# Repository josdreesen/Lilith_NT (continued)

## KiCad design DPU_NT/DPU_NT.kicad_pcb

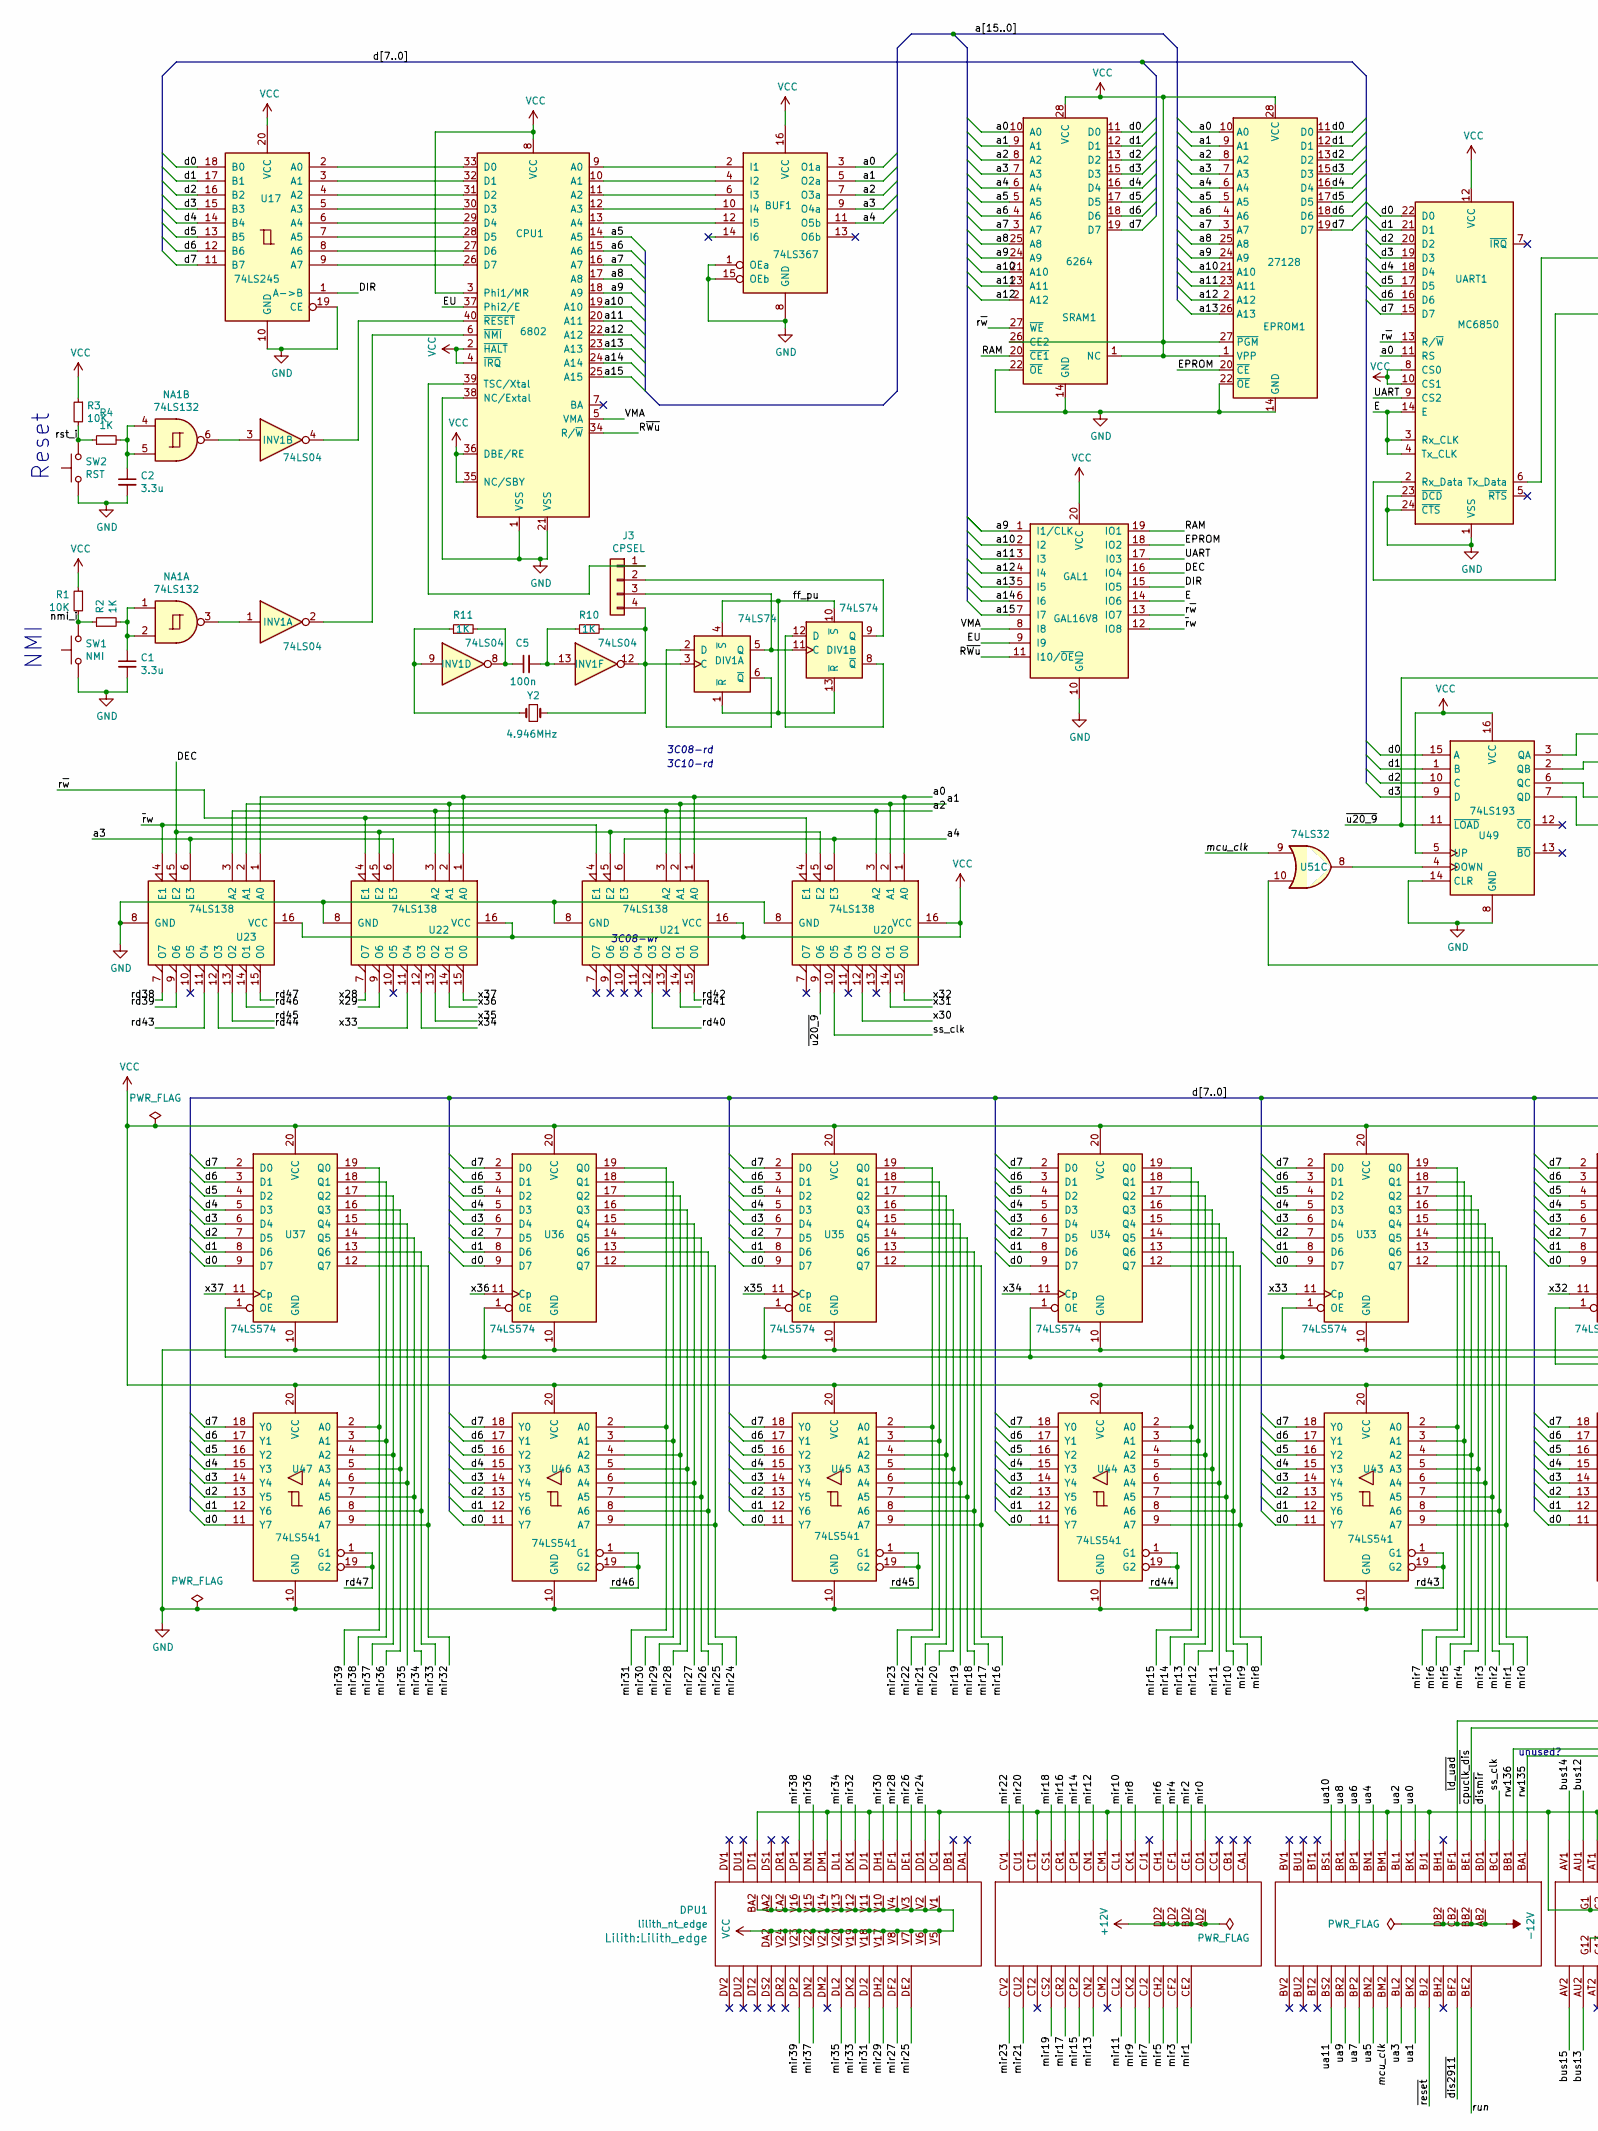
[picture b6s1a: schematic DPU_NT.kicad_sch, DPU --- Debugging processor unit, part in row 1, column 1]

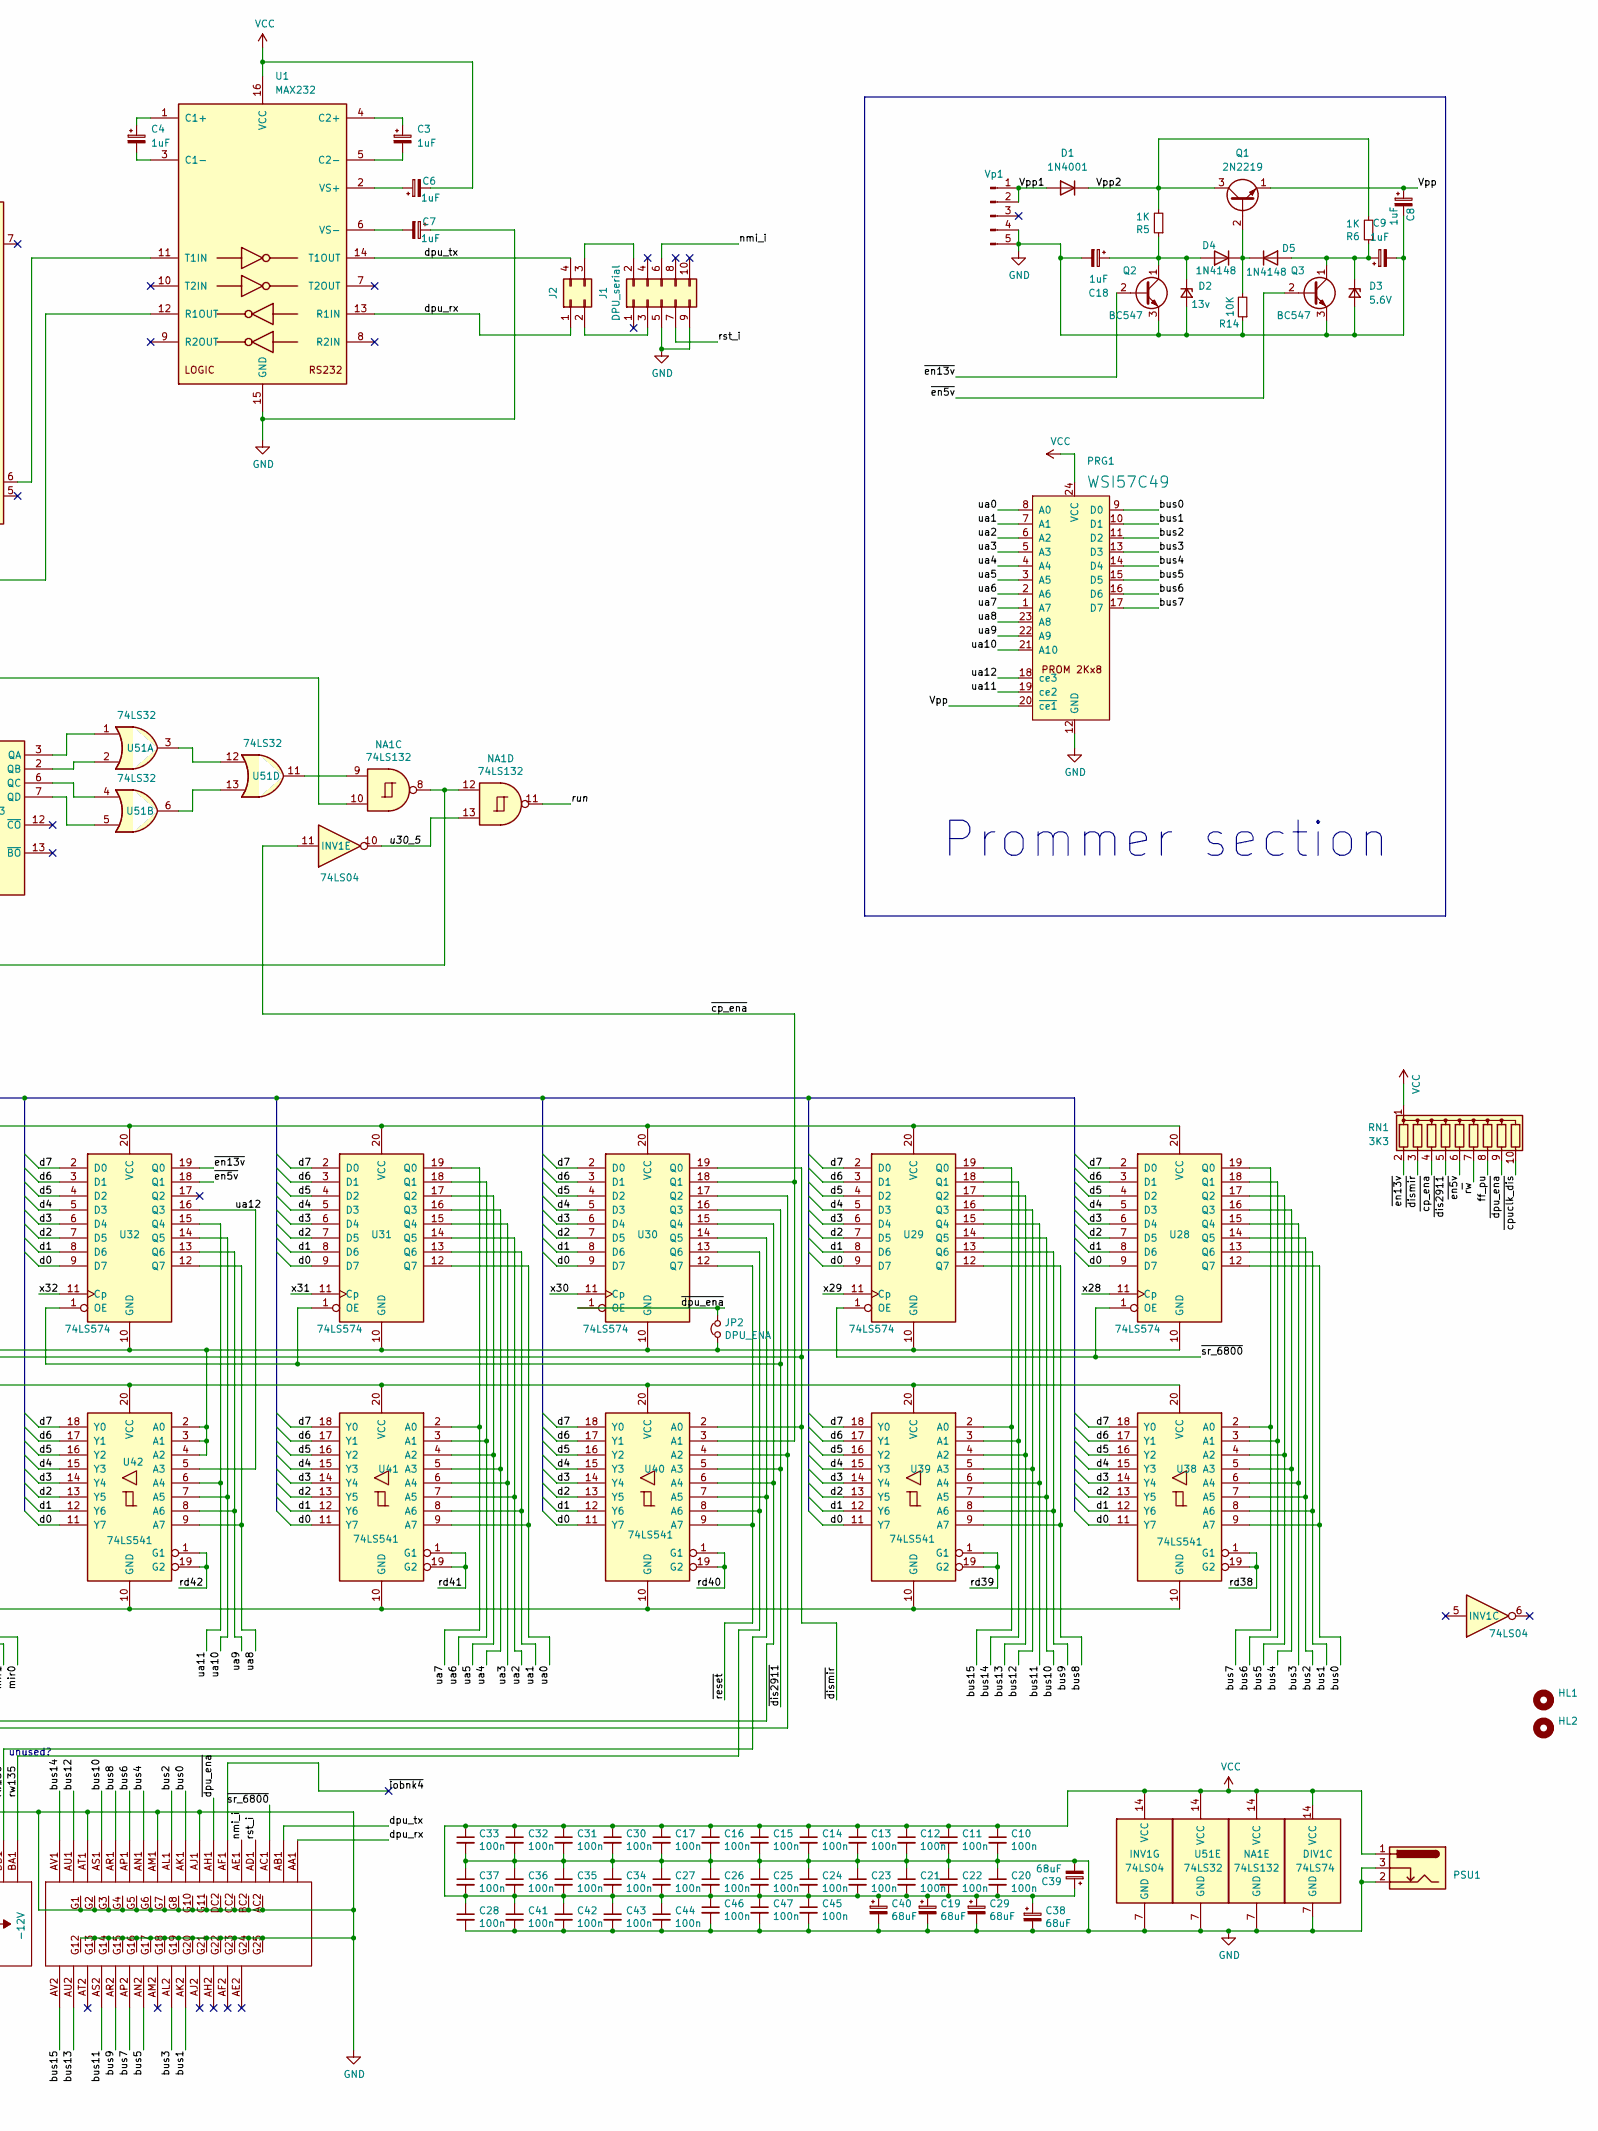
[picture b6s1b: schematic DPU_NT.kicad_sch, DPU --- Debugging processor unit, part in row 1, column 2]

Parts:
BUF1: 74LS367; DIP-16_W7.62mm
C1, C2: 3.3u; CP_Radial_D5.0mm_P2.50mm
C3, C4, C6, C7, C8, C9, C18: 1uF; CP_Radial_Tantal_D5.0mm_P2.50mm
C5: 100n; C_Rect_L7.0mm_W3.5mm_P5.00mm
C10, C11, C12, C13, C14, C15, C16, C17, C20, C21, C22, C23, C24, C25, C26, C27, C30, C31, C32, C33, C34, C35, C36, C37, C42, C45, C46, C47: 100n; C_1206_3216Metric_Pad1.33x1.80mm_HandSolder
C19, C29, C38, C39, C40: 68uF; CP_PHP
C28, C41, C43, C44: 100n; C_0805_2012Metric
CPU1: 6802; DIP-40_W15.24mm
D1: 1N4001; D_DO-35_SOD27_P7.62mm_Horizontal
D2: 13v; D_DO-35_SOD27_P7.62mm_Horizontal
D3: 5.6V; D_DO-35_SOD27_P7.62mm_Horizontal
D4, D5: 1N4148; D_DO-35_SOD27_P7.62mm_Horizontal
DIV1: 74LS74; DIP-14_W7.62mm
DPU1: lilith_nt_edge; Lilith_edge
EPROM1: 27128; DIP-28_W15.24mm
GAL1: GAL16V8; DIP-20_W7.62mm_Socket
HL1, HL2: MountingHole; Handle
INV1: 74LS04; DIP-14_W7.62mm_LongPads
J1: DPU_serial; PinHeader_2x05_P2.54mm_Vertical
J2: Conn_02x02_Counter_Clockwise; PinHeader_2x02_P2.54mm_Vertical
J3: CPSEL; PinHeader_1x04_P2.54mm_Vertical
JP2: DPU_ENA; PinHeader_1x02_P2.54mm_Vertical
NA1: 74LS132; DIP-14_W7.62mm
PRG1: WSI57C49; DuoDil24
PSU1: Barrel_Jack_Switch; BarrelJack_GCT_DCJ200-10-A_Horizontal
Q1: 2N2219; TO-39-3
Q2, Q3: BC547; TO-92_Inline
R1, R3, R14: 10K; R_Axial_DIN0207_L6.3mm_D2.5mm_P7.62mm_Horizontal
R2, R4, R5, R6, R10, R11: 1K; R_Axial_DIN0207_L6.3mm_D2.5mm_P7.62mm_Horizontal
RN1: 3K3; R_Array_SIP10
SRAM1: 6264; DIP-28_W15.24mm
SW1: NMI; SW_PUSH_6mm
SW2: RST; SW_PUSH_6mm
U1: MAX232; DIP-16_W7.62mm
U17: 74LS245; DIP-20_W7.62mm
U20, U21, U22, U23: 74LS138; DIP-16_W7.62mm
U28, U29, U30, U31, U32, U33, U34, U35, U36, U37: 74LS574; DIP-20_W7.62mm
U38, U39, U40, U41, U42, U43, U44, U45, U46, U47: 74LS541; DIP-20_W7.62mm
U49: 74LS193; DIP-16_W7.62mm
U51: 74LS32; DIP-14_W7.62mm
UART1: MC6850; DIP-24_W15.24mm
Vp1: Conn_01x05_Pin; PinHeader_1x05_P2.54mm_Horizontal
Y2: 4.946MHz; Crystal_HC52-8mm_Horizontal

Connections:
+12V: DPU1.AD2, DPU1.BD2, DPU1.CD2, DPU1.DD2
-12V: DPU1.AB2, DPU1.BB2, DPU1.CB2, DPU1.DB2
/DEC: GAL1.16 (IO4), U20.5 (E2), U21.5 (E2), U22.5 (E2), U23.5 (E2)
/DIR: GAL1.15 (IO5), U17.1 (A->B)
/E: GAL1.14 (IO6), UART1.3 (Rx_CLK), UART1.4 (Tx_CLK), UART1.14 (E)
/EPROM: EPROM1.20 (~CE), GAL1.18 (IO2)
/EU: CPU1.37 (Phi2/E), GAL1.9 (I9)
/RAM: GAL1.19 (IO1), SRAM1.20 (~CE1)
/R~Wu: CPU1.34 (R/~W), GAL1.11 (I10/~OE)
/UART: GAL1.17 (I03), UART1.9 (CS2)
/VMA: CPU1.5 (VMA), GAL1.8 (I8)
/Vpp: C8.1, PRG1.20 (~ce1), Q1.1 (E)
/Vpp1: D1.2 (A), Vp1.1, Vp1.2
/Vpp2: D1.1 (K), Q1.3 (C), R5.2, R6.2
/a0: BUF1.3 (O1a), EPROM1.10 (A0), SRAM1.10 (A0), U20.1 (A0), U21.1 (A0), U22.1 (A0), U23.1 (A0), UART1.11 (RS)
/a1: BUF1.5 (O2a), EPROM1.9 (A1), SRAM1.9 (A1), U20.2 (A1), U21.2 (A1), U22.2 (A1), U23.2 (A1)
/a2: BUF1.7 (O3a), EPROM1.8 (A2), SRAM1.8 (A2), U20.3 (A2), U21.3 (A2), U22.3 (A2), U23.3 (A2)
/a3: BUF1.9 (O4a), EPROM1.7 (A3), SRAM1.7 (A3), U22.6 (E3), U23.6 (E3)
/a4: BUF1.11 (O5b), EPROM1.6 (A4), SRAM1.6 (A4), U20.6 (E3), U21.6 (E3)
/a5: CPU1.14 (A5), EPROM1.5 (A5), SRAM1.5 (A5)
/a6: CPU1.15 (A6), EPROM1.4 (A6), SRAM1.4 (A6)
/a7: CPU1.16 (A7), EPROM1.3 (A7), SRAM1.3 (A7)
/a8: CPU1.17 (A8), EPROM1.25 (A8), SRAM1.25 (A8)
/a9: CPU1.18 (A9), EPROM1.24 (A9), GAL1.1 (I1/CLK), SRAM1.24 (A9)
/a10: CPU1.19 (A10), EPROM1.21 (A10), GAL1.2 (I2), SRAM1.21 (A10)
/a11: CPU1.20 (A11), EPROM1.23 (A11), GAL1.3 (I3), SRAM1.23 (A11)
/a12: CPU1.22 (A12), EPROM1.2 (A12), GAL1.4 (I4), SRAM1.2 (A12)
/a13: CPU1.23 (A13), EPROM1.26 (A13), GAL1.5 (I5)
/a14: CPU1.24 (A14), GAL1.6 (I6)
/a15: CPU1.25 (A15), GAL1.7 (I7)
/bus0: DPU1.AK1, PRG1.9 (D0), U28.12 (Q7), U38.9 (A7)
/bus1: DPU1.AK2, PRG1.10 (D1), U28.13 (Q6), U38.8 (A6)
/bus2: DPU1.AL1, PRG1.11 (D2), U28.14 (Q5), U38.7 (A5)
/bus3: DPU1.AL2, PRG1.13 (D3), U28.15 (Q4), U38.6 (A4)
/bus4: DPU1.AN1, PRG1.14 (D4), U28.16 (Q3), U38.5 (A3)
/bus5: DPU1.AN2, PRG1.15 (D5), U28.17 (Q2), U38.4 (A2)
/bus6: DPU1.AP1, PRG1.16 (D6), U28.18 (Q1), U38.3 (A1)
/bus7: DPU1.AP2, PRG1.17 (D7), U28.19 (Q0), U38.2 (A0)
/bus8: DPU1.AR1, U29.12 (Q7), U39.9 (A7)
/bus9: DPU1.AR2, U29.13 (Q6), U39.8 (A6)
/bus10: DPU1.AS1, U29.14 (Q5), U39.7 (A5)
/bus11: DPU1.AS2, U29.15 (Q4), U39.6 (A4)
/bus12: DPU1.AU1, U29.16 (Q3), U39.5 (A3)
/bus13: DPU1.AU2, U29.17 (Q2), U39.4 (A2)
/bus14: DPU1.AV1, U29.18 (Q1), U39.3 (A1)
/bus15: DPU1.AV2, U29.19 (Q0), U39.2 (A0)
/d0: EPROM1.11 (D0), SRAM1.11 (D0), U17.18 (B0), U28.9 (D7), U29.9 (D7), U30.9 (D7), U31.9 (D7), U32.9 (D7), U33.9 (D7), U34.9 (D7), U35.9 (D7), U36.9 (D7), U37.9 (D7), U38.11 (Y7), U39.11 (Y7), U40.11 (Y7), U41.11 (Y7), U42.11 (Y7), U43.11 (Y7), U44.11 (Y7), U45.11 (Y7), U46.11 (Y7), U47.11 (Y7), U49.15 (A), UART1.22 (D0)
/d1: EPROM1.12 (D1), SRAM1.12 (D1), U17.17 (B1), U28.8 (D6), U29.8 (D6), U30.8 (D6), U31.8 (D6), U32.8 (D6), U33.8 (D6), U34.8 (D6), U35.8 (D6), U36.8 (D6), U37.8 (D6), U38.12 (Y6), U39.12 (Y6), U40.12 (Y6), U41.12 (Y6), U42.12 (Y6), U43.12 (Y6), U44.12 (Y6), U45.12 (Y6), U46.12 (Y6), U47.12 (Y6), U49.1 (B), UART1.21 (D1)
/d2: EPROM1.13 (D2), SRAM1.13 (D2), U17.16 (B2), U28.7 (D5), U29.7 (D5), U30.7 (D5), U31.7 (D5), U32.7 (D5), U33.7 (D5), U34.7 (D5), U35.7 (D5), U36.7 (D5), U37.7 (D5), U38.13 (Y5), U39.13 (Y5), U40.13 (Y5), U41.13 (Y5), U42.13 (Y5), U43.13 (Y5), U44.13 (Y5), U45.13 (Y5), U46.13 (Y5), U47.13 (Y5), U49.10 (C), UART1.20 (D2)
/d3: EPROM1.15 (D3), SRAM1.15 (D3), U17.15 (B3), U28.6 (D4), U29.6 (D4), U30.6 (D4), U31.6 (D4), U32.6 (D4), U33.6 (D4), U34.6 (D4), U35.6 (D4), U36.6 (D4), U37.6 (D4), U38.14 (Y4), U39.14 (Y4), U40.14 (Y4), U41.14 (Y4), U42.14 (Y4), U43.14 (Y4), U44.14 (Y4), U45.14 (Y4), U46.14 (Y4), U47.14 (Y4), U49.9 (D), UART1.19 (D3)
/d4: EPROM1.16 (D4), SRAM1.16 (D4), U17.14 (B4), U28.5 (D3), U29.5 (D3), U30.5 (D3), U31.5 (D3), U32.5 (D3), U33.5 (D3), U34.5 (D3), U35.5 (D3), U36.5 (D3), U37.5 (D3), U38.15 (Y3), U39.15 (Y3), U40.15 (Y3), U41.15 (Y3), U42.15 (Y3), U43.15 (Y3), U44.15 (Y3), U45.15 (Y3), U46.15 (Y3), U47.15 (Y3), UART1.18 (D4)
/d5: EPROM1.17 (D5), SRAM1.17 (D5), U17.13 (B5), U28.4 (D2), U29.4 (D2), U30.4 (D2), U31.4 (D2), U32.4 (D2), U33.4 (D2), U34.4 (D2), U35.4 (D2), U36.4 (D2), U37.4 (D2), U38.16 (Y2), U39.16 (Y2), U40.16 (Y2), U41.16 (Y2), U42.16 (Y2), U43.16 (Y2), U44.16 (Y2), U45.16 (Y2), U46.16 (Y2), U47.16 (Y2), UART1.17 (D5)
/d6: EPROM1.18 (D6), SRAM1.18 (D6), U17.12 (B6), U28.3 (D1), U29.3 (D1), U30.3 (D1), U31.3 (D1), U32.3 (D1), U33.3 (D1), U34.3 (D1), U35.3 (D1), U36.3 (D1), U37.3 (D1), U38.17 (Y1), U39.17 (Y1), U40.17 (Y1), U41.17 (Y1), U42.17 (Y1), U43.17 (Y1), U44.17 (Y1), U45.17 (Y1), U46.17 (Y1), U47.17 (Y1), UART1.16 (D6)
/d7: EPROM1.19 (D7), SRAM1.19 (D7), U17.11 (B7), U28.2 (D0), U29.2 (D0), U30.2 (D0), U31.2 (D0), U32.2 (D0), U33.2 (D0), U34.2 (D0), U35.2 (D0), U36.2 (D0), U37.2 (D0), U38.18 (Y0), U39.18 (Y0), U40.18 (Y0), U41.18 (Y0), U42.18 (Y0), U43.18 (Y0), U44.18 (Y0), U45.18 (Y0), U46.18 (Y0), U47.18 (Y0), UART1.15 (D7)
/dpu_rx: DPU1.AA1, J2.1, U1.13 (R1IN)
/dpu_tx: DPU1.AB1, J2.4, U1.14 (T1OUT)
/ff_pu: DIV1.1 (~R), DIV1.4 (~S), DIV1.10 (~S), DIV1.13 (~R), RN1.8 (R7)
/mcu_clk: DPU1.BM2, U51.9
/mir0: DPU1.CD1, U33.12 (Q7), U43.9 (A7)
/mir1: DPU1.CE2, U33.13 (Q6), U43.8 (A6)
/mir2: DPU1.CE1, U33.14 (Q5), U43.7 (A5)
/mir3: DPU1.CF2, U33.15 (Q4), U43.6 (A4)
/mir4: DPU1.CF1, U33.16 (Q3), U43.5 (A3)
/mir5: DPU1.CH2, U33.17 (Q2), U43.4 (A2)
/mir6: DPU1.CH1, U33.18 (Q1), U43.3 (A1)
/mir7: DPU1.CJ2, U33.19 (Q0), U43.2 (A0)
/mir8: DPU1.CK1, U34.12 (Q7), U44.9 (A7)
/mir9: DPU1.CK2, U34.13 (Q6), U44.8 (A6)
/mir10: DPU1.CL1, U34.14 (Q5), U44.7 (A5)
/mir11: DPU1.CL2, U34.15 (Q4), U44.6 (A4)
/mir12: DPU1.CN1, U34.16 (Q3), U44.5 (A3)
/mir13: DPU1.CN2, U34.17 (Q2), U44.4 (A2)
/mir14: DPU1.CP1, U34.18 (Q1), U44.3 (A1)
/mir15: DPU1.CP2, U34.19 (Q0), U44.2 (A0)
/mir16: DPU1.CR1, U35.12 (Q7), U45.9 (A7)
/mir17: DPU1.CR2, U35.13 (Q6), U45.8 (A6)
/mir18: DPU1.CS1, U35.14 (Q5), U45.7 (A5)
/mir19: DPU1.CS2, U35.15 (Q4), U45.6 (A4)
/mir20: DPU1.CU1, U35.16 (Q3), U45.5 (A3)
/mir21: DPU1.CU2, U35.17 (Q2), U45.4 (A2)
/mir22: DPU1.CV1, U35.18 (Q1), U45.3 (A1)
/mir23: DPU1.CV2, U35.19 (Q0), U45.2 (A0)
/mir24: DPU1.DD1, U36.12 (Q7), U46.9 (A7)
/mir25: DPU1.DE2, U36.13 (Q6), U46.8 (A6)
/mir26: DPU1.DE1, U36.14 (Q5), U46.7 (A5)
/mir27: DPU1.DF2, U36.15 (Q4), U46.6 (A4)
/mir28: DPU1.DF1, U36.16 (Q3), U46.5 (A3)
/mir29: DPU1.DH2, U36.17 (Q2), U46.4 (A2)
/mir30: DPU1.DH1, U36.18 (Q1), U46.3 (A1)
/mir31: DPU1.DJ2, U36.19 (Q0), U46.2 (A0)
/mir32: DPU1.DK1, U37.12 (Q7), U47.9 (A7)
/mir33: DPU1.DK2, U37.13 (Q6), U47.8 (A6)
/mir34: DPU1.DL1, U37.14 (Q5), U47.7 (A5)
/mir35: DPU1.DL2, U37.15 (Q4), U47.6 (A4)
/mir36: DPU1.DN1, U37.16 (Q3), U47.5 (A3)
/mir37: DPU1.DN2, U37.17 (Q2), U47.4 (A2)
/mir38: DPU1.DP1, U37.18 (Q1), U47.3 (A1)
/mir39: DPU1.DP2, U37.19 (Q0), U47.2 (A0)
/nmi_i: DPU1.AE1, J1.6, R1.2, R2.1, SW1.2
/rd38: U23.7 (O7), U38.1 (G1), U38.19 (G2)
/rd39: U23.9 (O6), U39.1 (G1), U39.19 (G2)
/rd40: U21.12 (O3), U40.1 (G1), U40.19 (G2)
/rd41: U21.14 (O1), U41.1 (G1), U41.19 (G2)
/rd42: U21.15 (O0), U42.1 (G1), U42.19 (G2)
/rd43: U23.11 (O4), U43.1 (G1), U43.19 (G2)
/rd44: U23.12 (O3), U44.1 (G1), U44.19 (G2)
/rd45: U23.13 (O2), U45.1 (G1), U45.19 (G2)
/rd46: U23.14 (O1), U46.1 (G1), U46.19 (G2)
/rd47: U23.15 (O0), U47.1 (G1), U47.19 (G2)
/rst_i: DPU1.AD1, J1.7, R3.2, R4.1, SW2.2
/run: DPU1.BE2, NA1.11
/rw135: DPU1.BA1, U30.13 (Q6), U40.8 (A6)
/rw136: DPU1.BB1, U30.14 (Q5), U40.7 (A5)
/r~w: GAL1.13 (IO7), RN1.7 (R6), SRAM1.27 (~WE), U20.4 (E1), U22.4 (E1), UART1.13 (R/~W)
/ss_clk: DPU1.BC1, U20.10 (O5)
/u30_5: INV1.10, NA1.13
/ua0: DPU1.BK1, PRG1.8 (A0), U31.12 (Q7), U41.9 (A7)
/ua1: DPU1.BK2, PRG1.7 (A1), U31.13 (Q6), U41.8 (A6)
/ua2: DPU1.BL1, PRG1.6 (A2), U31.14 (Q5), U41.7 (A5)
/ua3: DPU1.BL2, PRG1.5 (A3), U31.15 (Q4), U41.6 (A4)
/ua4: DPU1.BN1, PRG1.4 (A4), U31.16 (Q3), U41.5 (A3)
/ua5: DPU1.BN2, PRG1.3 (A5), U31.17 (Q2), U41.4 (A2)
/ua6: DPU1.BP1, PRG1.2 (A6), U31.18 (Q1), U41.3 (A1)
/ua7: DPU1.BP2, PRG1.1 (A7), U31.19 (Q0), U41.2 (A0)
/ua8: DPU1.BR1, PRG1.23 (A8), U32.12 (Q7), U42.9 (A7)
/ua9: DPU1.BR2, PRG1.22 (A9), U32.13 (Q6), U42.8 (A6)
/ua10: DPU1.BS1, PRG1.21 (A10), U32.14 (Q5), U42.7 (A5)
/ua11: DPU1.BS2, PRG1.19 (ce2), U32.15 (Q4), U42.6 (A4)
/ua12: PRG1.18 (ce3), U32.16 (Q3), U42.5 (A3)
/x28: U22.7 (O7), U28.11 (Cp)
/x29: U22.9 (O6), U29.11 (Cp)
/x30: U20.12 (O3), U30.11 (Cp)
/x31: U20.14 (O1), U31.11 (Cp)
/x32: U20.15 (O0), U32.11 (Cp)
/x33: U22.11 (O4), U33.11 (Cp)
/x34: U22.12 (O3), U34.11 (Cp)
/x35: U22.13 (O2), U35.11 (Cp)
/x36: U22.14 (O1), U36.11 (Cp)
/x37: U22.15 (O0), U37.11 (Cp)
/~cp_ena: INV1.11, RN1.4 (R3), U30.18 (Q1), U40.3 (A1)
/~cpuclk_dis: DPU1.BE1, RN1.10 (R9), U30.17 (Q2), U40.4 (A2)
/~dis2911: DPU1.BF2, RN1.5 (R4), U30.16 (Q3), U31.1 (OE), U32.1 (OE), U40.5 (A3)
/~dismir: DPU1.BD1, RN1.3 (R2), U30.19 (Q0), U33.1 (OE), U34.1 (OE), U35.1 (OE), U36.1 (OE), U37.1 (OE), U40.2 (A0)
/~dpu_ena: DPU1.AH1, JP2.2, RN1.9 (R8), U30.1 (OE)
/~en5v: Q3.2 (B), RN1.6 (R5), U32.18 (Q1)
/~en13v: Q2.2 (B), RN1.2 (R1), U32.19 (Q0)
/~iobnk4: DPU1.AF1
/~ld_uad: DPU1.BF1, U30.15 (Q4), U40.6 (A4)
/~reset: DPU1.BJ2, U30.12 (Q7), U40.9 (A7)
/~rw: GAL1.12 (IO8), U21.4 (E1), U23.4 (E1)
/~sr_6800: DPU1.AC1, U28.1 (OE), U29.1 (OE)
/~u20_9: NA1.10, U20.9 (O6), U49.11 (~LOAD)
GND: BUF1.1 (OEa), BUF1.8 (GND), BUF1.15 (OEb), C1.2, C2.2, C7.1, C8.2, C9.2, C10.2, C11.2, C12.2, C13.2, C14.2, C15.2, C16.2, C17.2, C18.2, C19.2, C20.1, C21.1, C22.1, C23.1, C24.1, C25.1, C26.1, C27.1, C28.2, C29.2, C30.2, C31.2, C32.2, C33.2, C34.1, C35.1, C36.1, C37.1, C38.2, C39.2, C40.2, C41.2, C42.2, C43.2, C44.2, C45.2, C46.2, C47.2, CPU1.1 (VSS), CPU1.21 (VSS), CPU1.38 (NC/Extal), D2.2 (A), D3.2 (A), DIV1.7 (GND), DPU1.AC2, DPU1.AJ1, DPU1.AM1, DPU1.AT1, DPU1.BC2, DPU1.BJ1, DPU1.BM1, DPU1.CC2, DPU1.CM1, DPU1.CT1, DPU1.DC1, DPU1.DC2, DPU1.DJ1, DPU1.DM1, DPU1.DT1, DPU1.G1 (GND), DPU1.G2 (GND), DPU1.G3 (GND), DPU1.G4 (GND), DPU1.G5 (GND), DPU1.G6 (GND), DPU1.G7 (GND), DPU1.G8 (GND), DPU1.G10, DPU1.G11, DPU1.G12, DPU1.G13, DPU1.G14, DPU1.G15, DPU1.G16, DPU1.G17, DPU1.G18, DPU1.G19, DPU1.G20, DPU1.G21, DPU1.G22, DPU1.G23, DPU1.G24, DPU1.G25, EPROM1.14 (GND), EPROM1.22 (~OE), GAL1.10 (GND), INV1.7 (GND), J1.5, J1.9, JP2.1, NA1.7 (GND), PRG1.12 (GND), PSU1.2, PSU1.3, Q2.3 (E), Q3.3 (E), R14.1, SRAM1.14 (GND), SRAM1.22 (~OE), SW1.1, SW2.1, U1.15 (GND), U17.10 (GND), U17.19 (CE), U20.8 (GND), U21.8 (GND), U22.8 (GND), U23.8 (GND), U28.10 (GND), U29.10 (GND), U30.10 (GND), U31.10 (GND), U32.10 (GND), U33.10 (GND), U34.10 (GND), U35.10 (GND), U36.10 (GND), U37.10 (GND), U38.10 (GND), U39.10 (GND), U40.10 (GND), U41.10 (GND), U42.2 (A0), U42.3 (A1), U42.4 (A2), U42.10 (GND), U43.10 (GND), U44.10 (GND), U45.10 (GND), U46.10 (GND), U47.10 (GND), U49.8 (GND), U49.14 (CLR), U51.7 (GND), UART1.1 (VSS), UART1.23 (~DCD), UART1.24 (~CTS), Vp1.4, Vp1.5
unnamed: BUF1.2 (I1), CPU1.9 (A0)
unnamed: BUF1.4 (I2), CPU1.10 (A1)
unnamed: BUF1.6 (I3), CPU1.11 (A2)
unnamed: BUF1.10 (I4), CPU1.12 (A3)
unnamed: BUF1.12 (I5), CPU1.13 (A4)
unnamed: C1.1, NA1.1, NA1.2, R2.2
unnamed: C2.1, NA1.4, NA1.5, R4.2
unnamed: C5.1, INV1.8, R11.2
unnamed: C5.2, INV1.13, R10.1
unnamed: CPU1.33 (D0), U17.2 (A0)
unnamed: CPU1.32 (D1), U17.3 (A1)
unnamed: CPU1.31 (D2), U17.4 (A2)
unnamed: CPU1.30 (D3), U17.5 (A3)
unnamed: CPU1.29 (D4), U17.6 (A4)
unnamed: CPU1.28 (D5), U17.7 (A5)
unnamed: CPU1.27 (D6), U17.8 (A6)
unnamed: CPU1.26 (D7), U17.9 (A7)
unnamed: CPU1.39 (TSC/Xtal), J3.1
unnamed: CPU1.6 (~NMI), INV1.2
unnamed: CPU1.40 (~RESET), INV1.4
unnamed: C18.1, D2.1 (K), D4.2 (A), Q2.1 (C), R5.1
unnamed: C9.1, D3.1 (K), D5.2 (A), Q3.1 (C), R6.1
unnamed: D4.1 (K), D5.1 (K), Q1.2 (B), R14.2
unnamed: DIV1.3 (C), INV1.12, J3.4, R10.2, Y2.1
unnamed: DIV1.2 (D), DIV1.6 (~Q)
unnamed: DIV1.5 (Q), DIV1.11 (C), J3.3
unnamed: DIV1.8 (~Q), DIV1.12 (D)
unnamed: DIV1.9 (Q), J3.2
unnamed: INV1.1, NA1.3
unnamed: INV1.3, NA1.6
unnamed: INV1.9, R11.1, Y2.2
unnamed: J1.2, J2.3
unnamed: J1.3, J2.2
unnamed: NA1.9, U51.11
unnamed: NA1.8, NA1.12, U51.10
unnamed: C4.1, U1.1 (C1+)
unnamed: C4.2, U1.3 (C1-)
unnamed: C3.1, U1.4 (C2+)
unnamed: C3.2, U1.5 (C2-)
unnamed: U1.12 (R1OUT), UART1.2 (Rx_Data)
unnamed: U1.11 (T1IN), UART1.6 (Tx_Data)
unnamed: C6.1, U1.2 (VS+)
unnamed: C7.2, U1.6 (VS-)
unnamed: U49.4 (DOWN), U51.8
unnamed: U49.3 (QA), U51.1
unnamed: U49.2 (QB), U51.2
unnamed: U49.6 (QC), U51.4
unnamed: U49.7 (QD), U51.5
unnamed: U51.3, U51.12
unnamed: U51.6, U51.13
VCC: BUF1.16 (VCC), C6.2, C10.1, C11.1, C12.1, C13.1, C14.1, C15.1, C16.1, C17.1, C19.1, C20.2, C21.2, C22.2, C23.2, C24.2, C25.2, C26.2, C27.2, C28.1, C29.1, C30.1, C31.1, C32.1, C33.1, C34.2, C35.2, C36.2, C37.2, C38.1, C39.1, C40.1, C41.1, C42.1, C43.1, C44.1, C45.1, C46.1, C47.1, CPU1.2 (~HALT), CPU1.3 (Phi1/MR), CPU1.4 (~IRQ), CPU1.8 (VCC), CPU1.35 (NC/SBY), CPU1.36 (DBE/RE), DIV1.14 (VCC), DPU1.AA2, DPU1.BA2, DPU1.CA2, DPU1.DA2, DPU1.V1 (VCC), DPU1.V2 (VCC), DPU1.V3 (VCC), DPU1.V4 (VCC), DPU1.V5 (VCC), DPU1.V6 (VCC), DPU1.V7 (VCC), DPU1.V8 (VCC), DPU1.V10, DPU1.V11, DPU1.V12, DPU1.V13, DPU1.V14, DPU1.V15, DPU1.V16, DPU1.V17, DPU1.V18, DPU1.V19, DPU1.V20, DPU1.V21, DPU1.V22, DPU1.V23, DPU1.V24, EPROM1.1 (VPP), EPROM1.27 (~PGM), EPROM1.28 (VCC), GAL1.20 (VCC), INV1.14 (VCC), NA1.14 (VCC), PRG1.24 (VCC), PSU1.1, R1.1, R3.1, RN1.1 (common), SRAM1.1 (NC), SRAM1.26 (CE2), SRAM1.28 (VCC), U1.16 (VCC), U17.20 (VCC), U20.16 (VCC), U21.16 (VCC), U22.16 (VCC), U23.16 (VCC), U28.20 (VCC), U29.20 (VCC), U30.20 (VCC), U31.20 (VCC), U32.20 (VCC), U33.20 (VCC), U34.20 (VCC), U35.20 (VCC), U36.20 (VCC), U37.20 (VCC), U38.20 (VCC), U39.20 (VCC), U40.20 (VCC), U41.20 (VCC), U42.20 (VCC), U43.20 (VCC), U44.20 (VCC), U45.20 (VCC), U46.20 (VCC), U47.20 (VCC), U49.5 (UP), U49.16 (VCC), U51.14 (VCC), UART1.8 (CS0), UART1.10 (CS1), UART1.12 (VCC)

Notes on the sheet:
3C08-wr
Reset
NMI
unused?
Prommer section
3C08-rd
3C10-rd

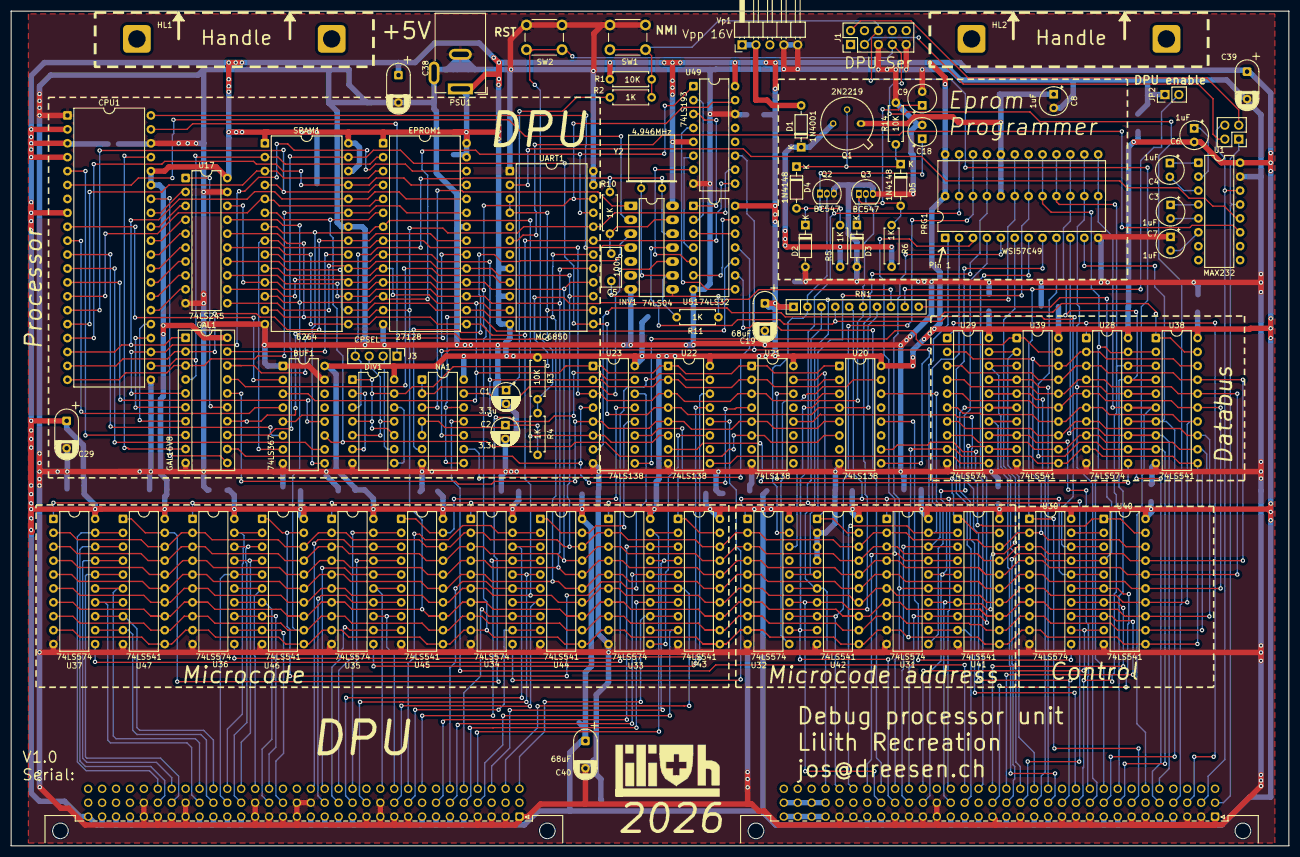
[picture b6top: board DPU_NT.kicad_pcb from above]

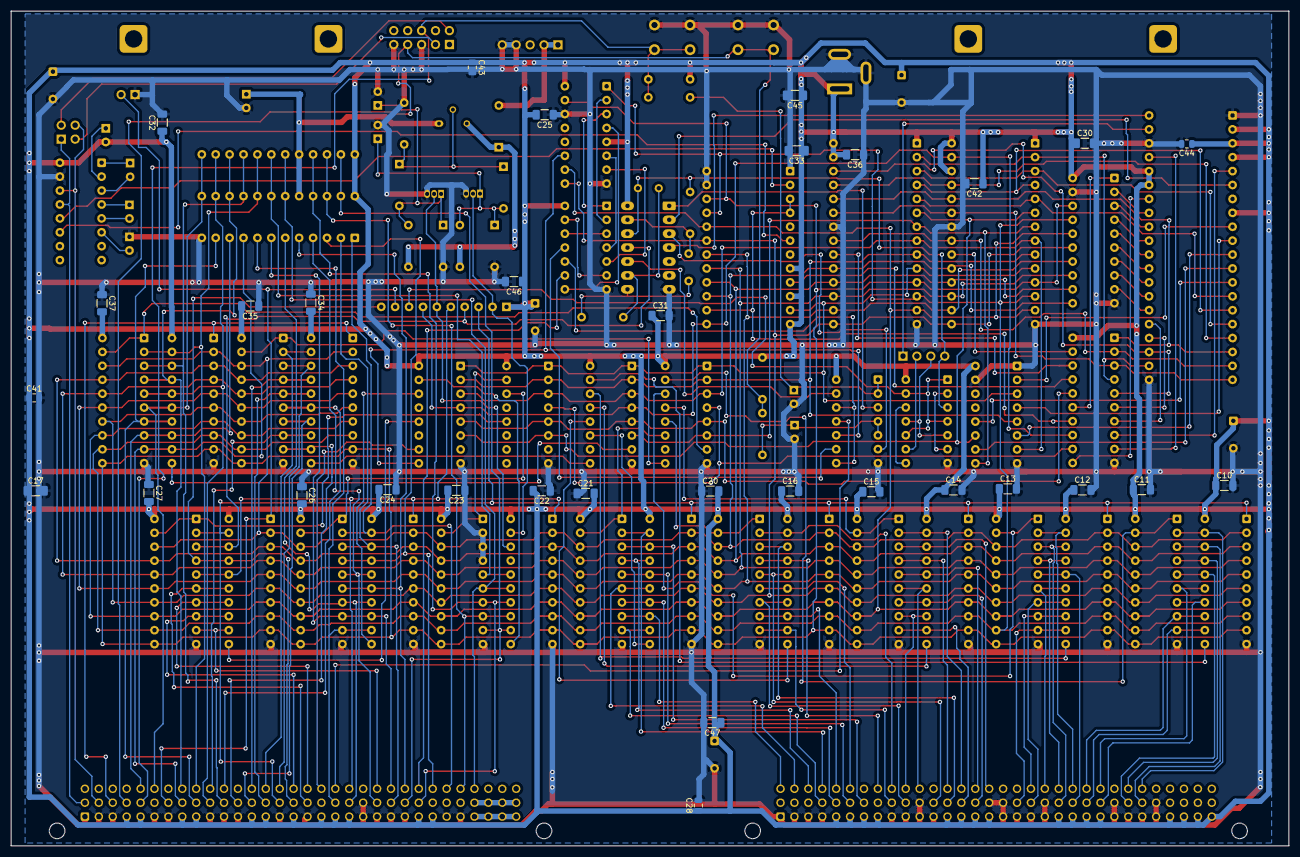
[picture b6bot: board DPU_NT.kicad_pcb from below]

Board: 2 copper layers, 233.3 x 152.4 mm, 115 parts (32 on the bottom side), 203 nets.
